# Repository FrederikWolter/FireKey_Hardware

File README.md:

# FireKey - Hardware

This student research project named *FireKey* is part of the winter semester 2022 and summer semester 2023 in the
Applied Computer Science course at DHBW Mannheim. The aim is to create a macro keyboard with individually configurable
keys that allow the input of simple key combinations up to more complex sequences.

This repository is used for developing the *hardware* of *FireKey*. The corresponding firmware is developed in
the [FireKey_Firmware](https://github.com/FrederikWolter/FireKey_Firmware) repository and the configuration software
in [FireKey_Configurator](https://github.com/FrederikWolter/FireKey_Configurator).

## Structure

### *PCB*

Work in progress TODO

### *PCB_theory*

Work in progress TODO

### *3D_printing*

Work in progress TODO

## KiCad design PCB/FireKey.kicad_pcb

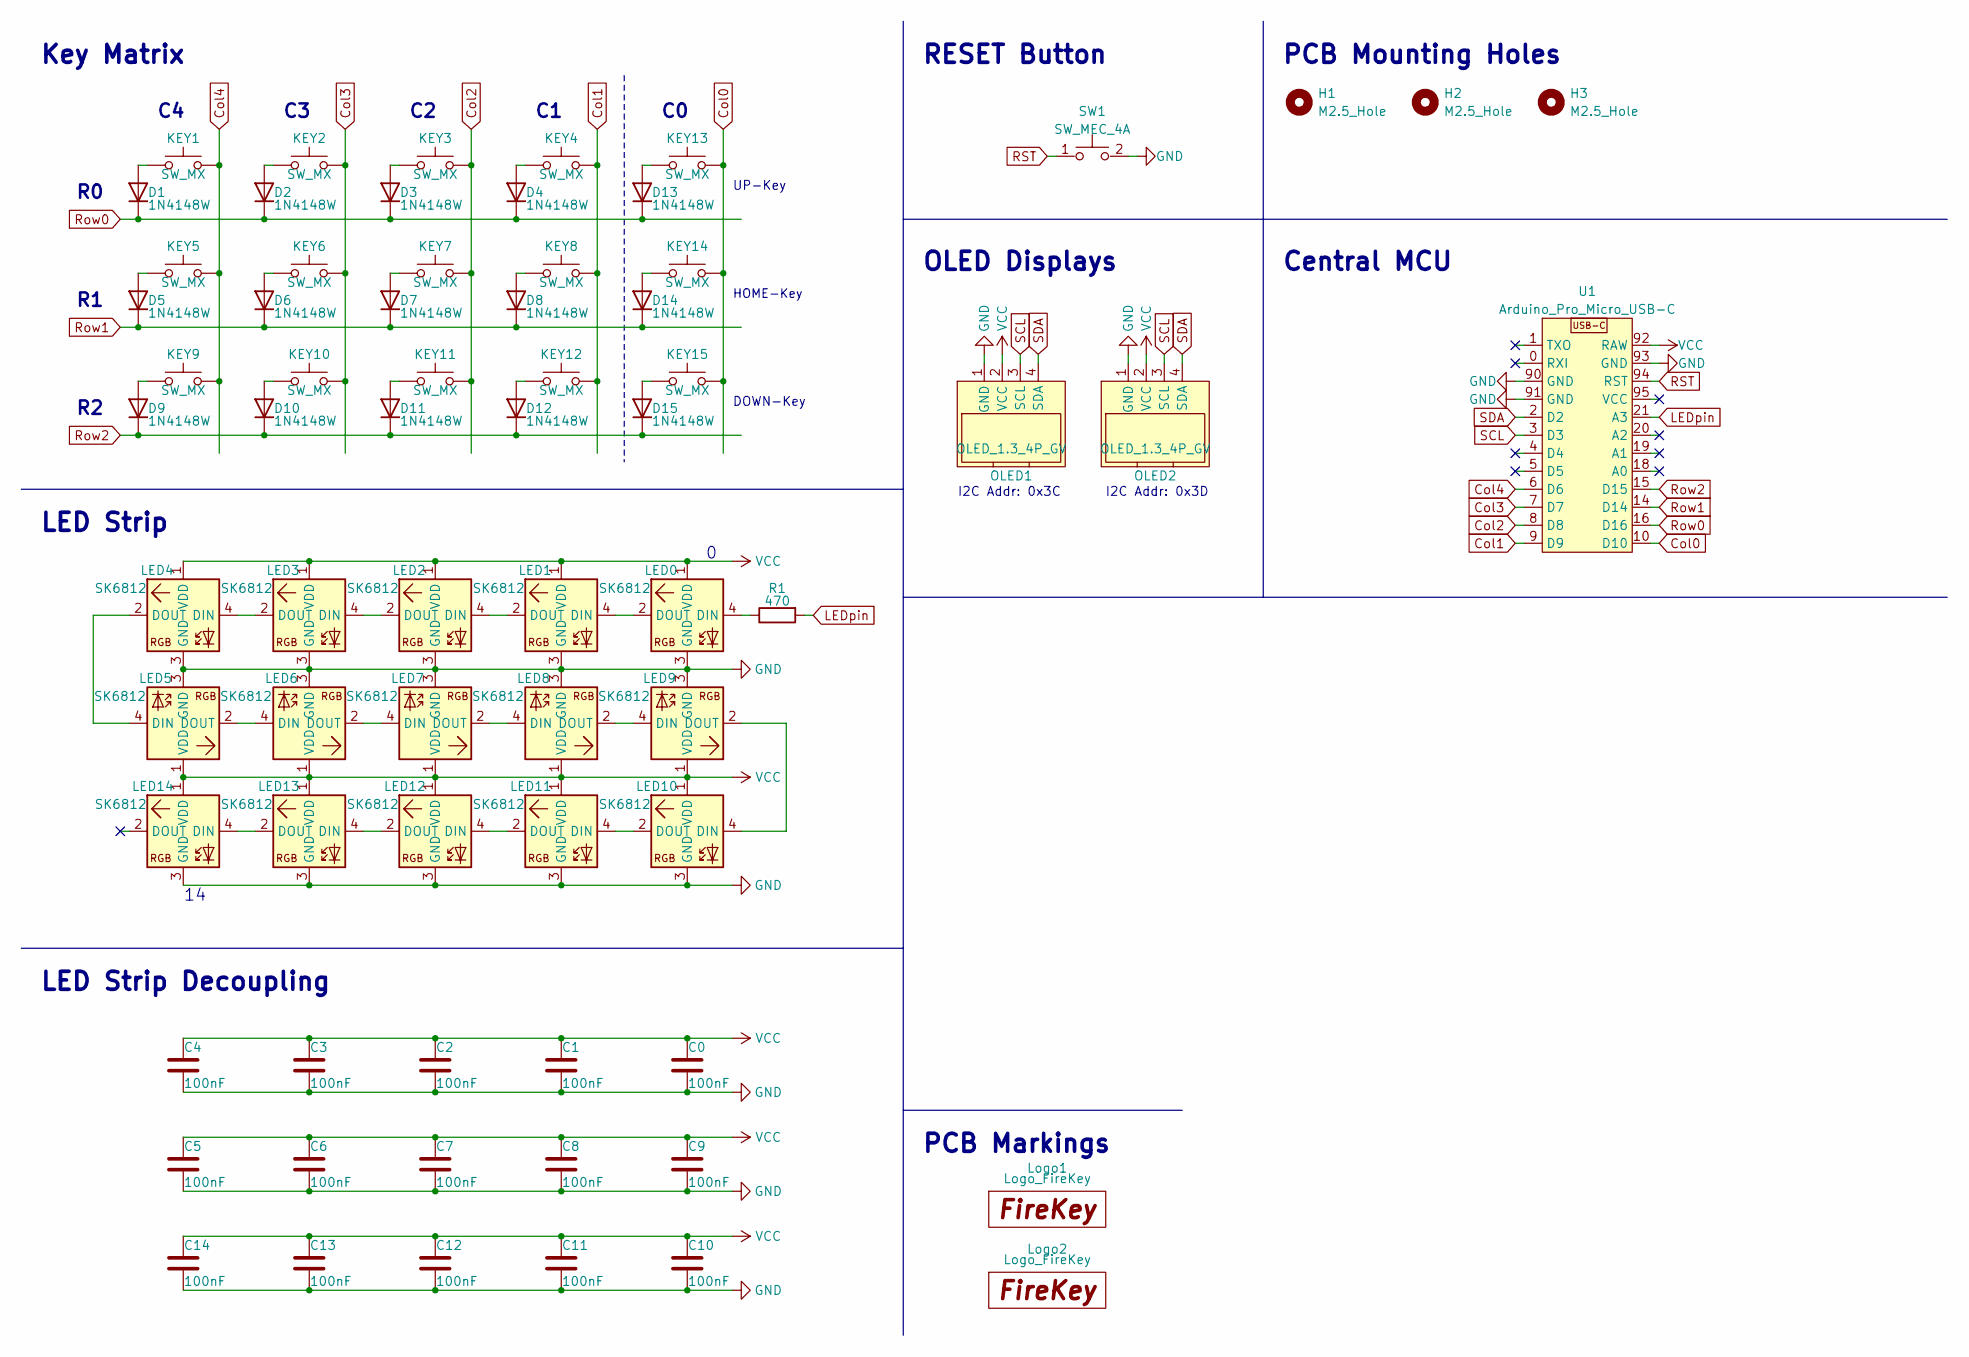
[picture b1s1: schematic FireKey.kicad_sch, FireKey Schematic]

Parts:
C0, C1, C2, C3, C4, C5, C6, C7, C8, C9, C10, C11, C12, C13, C14: 100nF; C_0603_1608Metric_Pad1.08x0.95mm_HandSolder; Part# C694249
D1, D2, D3, D4, D5, D6, D7, D8, D9, D10, D11, D12, D13, D14, D15: 1N4148W; D_SOD-123; Part# C2892570
H1, H2, H3: M2.5_Hole; MountingHole_2.7mm_M2.5
KEY1, KEY2, KEY3, KEY4, KEY5, KEY6, KEY7, KEY8, KEY9, KEY10, KEY11, KEY12, KEY13, KEY14, KEY15: SW_MX; SW_Cherry_MX_1.00u_PCB_CleanFront
LED0, LED1, LED2, LED3, LED4, LED5, LED6, LED7, LED8, LED9, LED10, LED11, LED12, LED13, LED14: SK6812; DY-S352818-6812-2T; Part# C524051
Logo1: Logo_FireKey; Logo_FireKey_22x6.4
Logo2: Logo_FireKey; Logo_FireKey_12x3.5
OLED1, OLED2: OLED_1.3_4P_GV; OLED_1.3_4P_M2.5Holes_CleanFront
R1: 470; R_0603_1608Metric_Pad0.98x0.95mm_HandSolder; Part# C23179
SW1: SW_MEC_4A; SW_SPST_TL3342; Part# C2888878
U1: Arduino_Pro_Micro_USB-C; Arduino_Pro_Micro_USB-C_CleanFront

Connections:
Col0: KEY13.2 (B), KEY14.2 (B), KEY15.2 (B), U1.10 (D10)
Col1: KEY4.2 (B), KEY8.2 (B), KEY12.2 (B), U1.9 (D9)
Col2: KEY3.2 (B), KEY7.2 (B), KEY11.2 (B), U1.8 (D8)
Col3: KEY2.2 (B), KEY6.2 (B), KEY10.2 (B), U1.7 (D7)
Col4: KEY1.2 (B), KEY5.2 (B), KEY9.2 (B), U1.6 (D6)
GND: C0.2, C1.2, C2.2, C3.2, C4.2, C5.2, C6.2, C7.2, C8.2, C9.2, C10.2, C11.2, C12.2, C13.2, C14.2, LED0.3 (GND), LED1.3 (GND), LED2.3 (GND), LED3.3 (GND), LED4.3 (GND), LED5.3 (GND), LED6.3 (GND), LED7.3 (GND), LED8.3 (GND), LED9.3 (GND), LED10.3 (GND), LED11.3 (GND), LED12.3 (GND), LED13.3 (GND), LED14.3 (GND), OLED1.1 (GND), OLED2.1 (GND), SW1.2, U1.90 (GND), U1.91 (GND), U1.93 (GND)
LEDpin: R1.2, U1.21 (A3)
unnamed: D1.2 (A), KEY1.1 (A)
unnamed: D2.2 (A), KEY2.1 (A)
unnamed: D3.2 (A), KEY3.1 (A)
unnamed: D4.2 (A), KEY4.1 (A)
unnamed: D5.2 (A), KEY5.1 (A)
unnamed: D6.2 (A), KEY6.1 (A)
unnamed: D7.2 (A), KEY7.1 (A)
unnamed: D8.2 (A), KEY8.1 (A)
unnamed: D9.2 (A), KEY9.1 (A)
unnamed: D10.2 (A), KEY10.1 (A)
unnamed: D11.2 (A), KEY11.1 (A)
unnamed: D12.2 (A), KEY12.1 (A)
unnamed: D13.2 (A), KEY13.1 (A)
unnamed: D14.2 (A), KEY14.1 (A)
unnamed: D15.2 (A), KEY15.1 (A)
unnamed: LED0.2 (DOUT), LED1.4 (DIN)
unnamed: LED0.4 (DIN), R1.1
unnamed: LED1.2 (DOUT), LED2.4 (DIN)
unnamed: LED2.2 (DOUT), LED3.4 (DIN)
unnamed: LED3.2 (DOUT), LED4.4 (DIN)
unnamed: LED4.2 (DOUT), LED5.4 (DIN)
unnamed: LED5.2 (DOUT), LED6.4 (DIN)
unnamed: LED6.2 (DOUT), LED7.4 (DIN)
unnamed: LED7.2 (DOUT), LED8.4 (DIN)
unnamed: LED8.2 (DOUT), LED9.4 (DIN)
unnamed: LED10.2 (DOUT), LED11.4 (DIN)
unnamed: LED9.2 (DOUT), LED10.4 (DIN)
unnamed: LED11.2 (DOUT), LED12.4 (DIN)
unnamed: LED12.2 (DOUT), LED13.4 (DIN)
unnamed: LED13.2 (DOUT), LED14.4 (DIN)
RST: SW1.1, U1.94 (RST)
Row0: D1.1 (K), D2.1 (K), D3.1 (K), D4.1 (K), D13.1 (K), U1.16 (D16)
Row1: D5.1 (K), D6.1 (K), D7.1 (K), D8.1 (K), D14.1 (K), U1.14 (D14)
Row2: D9.1 (K), D10.1 (K), D11.1 (K), D12.1 (K), D15.1 (K), U1.15 (D15)
SCL: OLED1.3 (SCL), OLED2.3 (SCL), U1.3 (D3)
SDA: OLED1.4 (SDA), OLED2.4 (SDA), U1.2 (D2)
VCC: C0.1, C1.1, C2.1, C3.1, C4.1, C5.1, C6.1, C7.1, C8.1, C9.1, C10.1, C11.1, C12.1, C13.1, C14.1, LED0.1 (VDD), LED1.1 (VDD), LED2.1 (VDD), LED3.1 (VDD), LED4.1 (VDD), LED5.1 (VDD), LED6.1 (VDD), LED7.1 (VDD), LED8.1 (VDD), LED9.1 (VDD), LED10.1 (VDD), LED11.1 (VDD), LED12.1 (VDD), LED13.1 (VDD), LED14.1 (VDD), OLED1.2 (VCC), OLED2.2 (VCC), U1.92 (RAW)

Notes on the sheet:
RESET Button
DOWN-Key
UP-Key
LED Strip
HOME-Key
I2C Addr: 0x3C
PCB Mounting Holes
Key Matrix
I2C Addr: 0x3D
OLED Displays
Central MCU
LED Strip Decoupling
PCB Markings

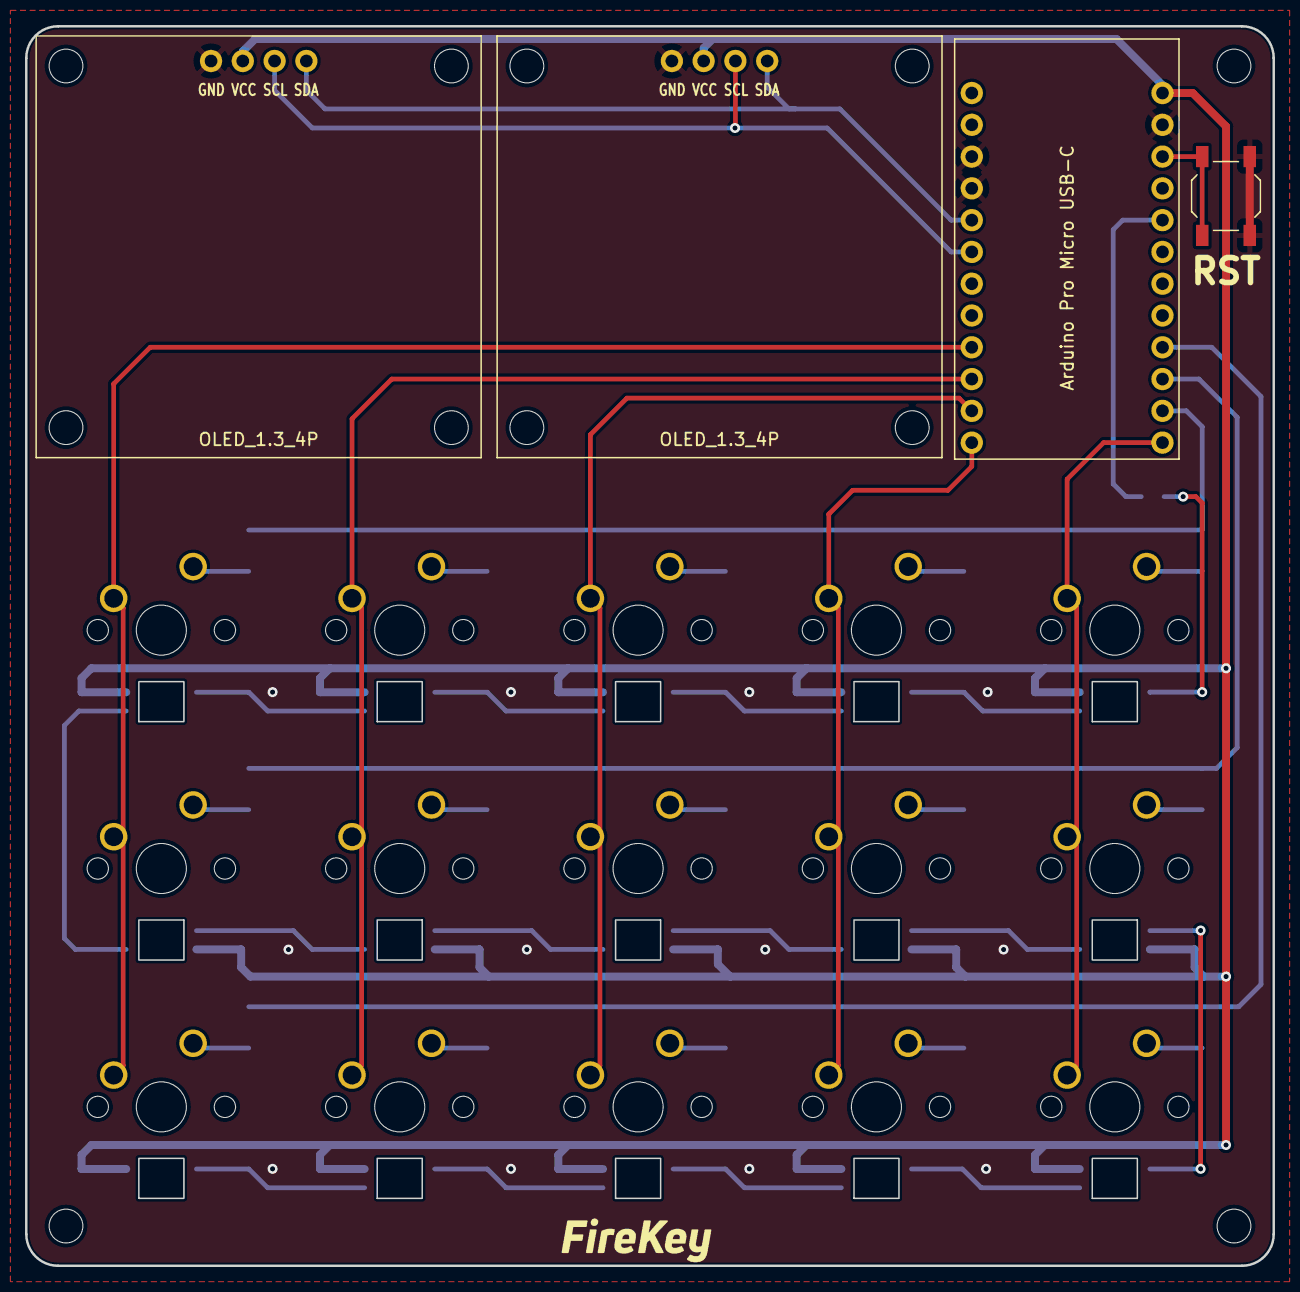
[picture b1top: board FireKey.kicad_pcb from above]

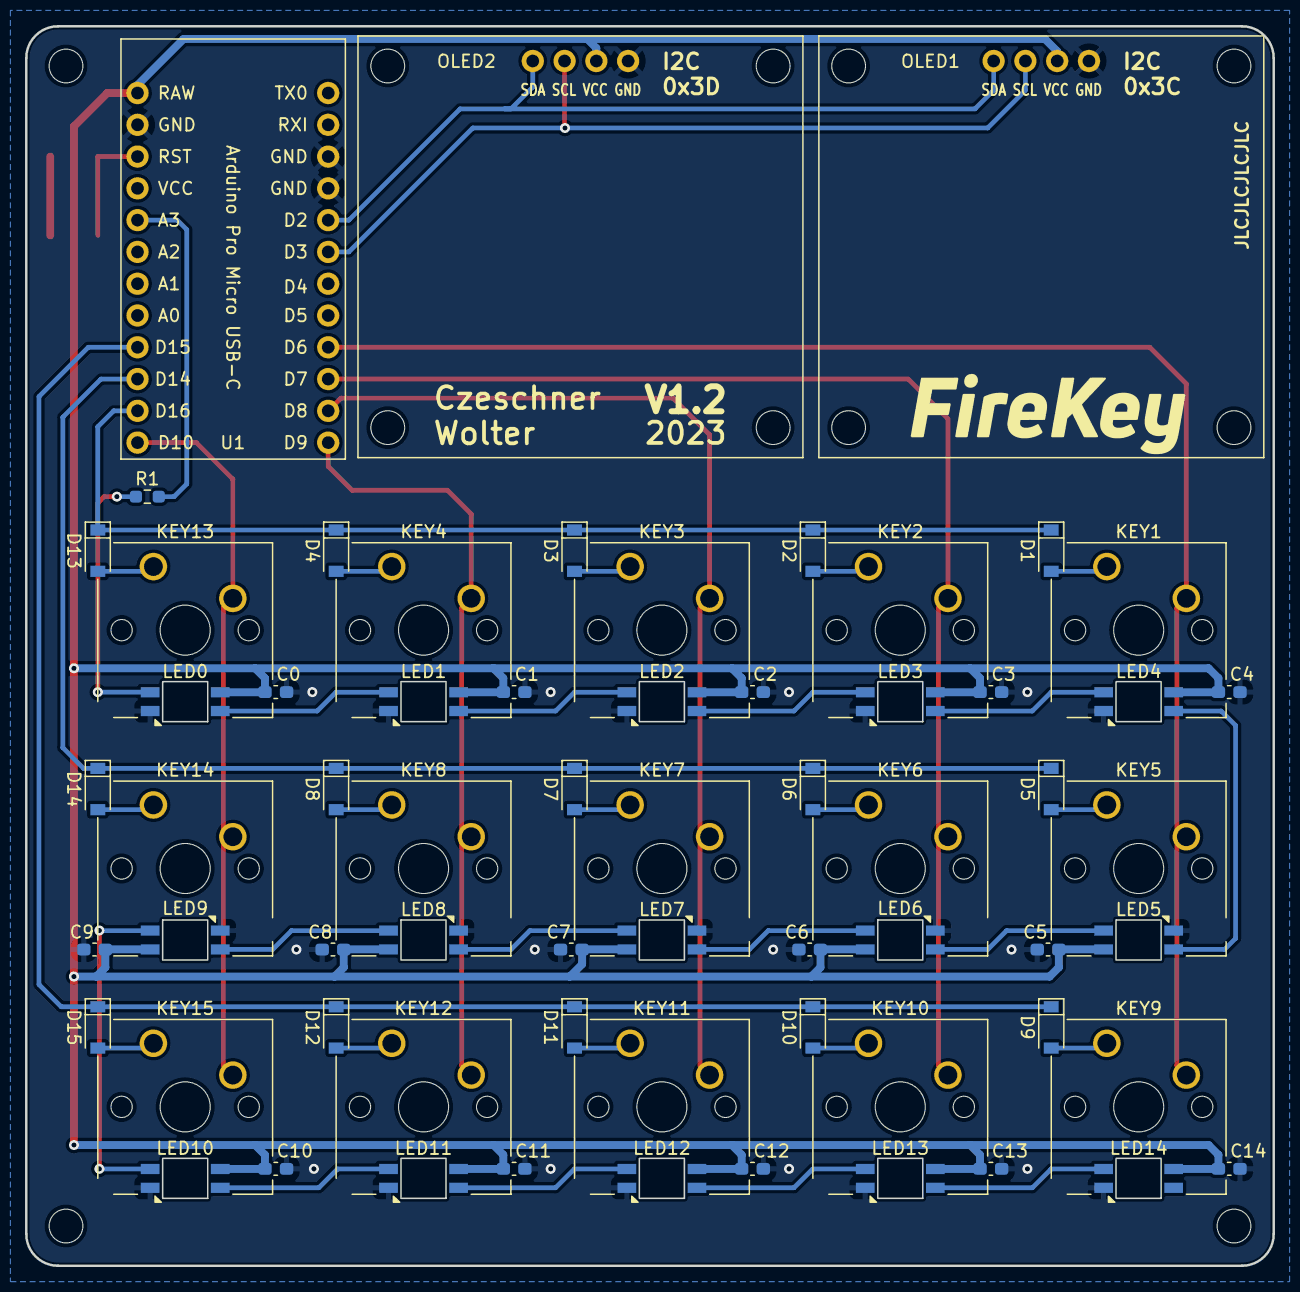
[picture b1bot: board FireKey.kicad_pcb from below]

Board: 2 copper layers, 99.7 x 99.1 mm, 70 parts (47 on the bottom side), 44 nets.

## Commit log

2022-11-13 added .gitignore for KiCad files
2022-11-13 add empty KiCad project
2022-11-13 Started recreating V0 schematic in KiCad
2022-11-14 added custom libraries
2022-11-14 worked on schematic
2022-11-14 worked on schematic; added net labels
2022-11-14 change .gitignore to not ignore BOM files
2022-11-14 finished recreating V0 schematic in KiCad
2022-11-14 generated current version of BOM
2022-11-14 updated and worked on BOM
2022-11-14 BOM management; started footprint assignment
2022-11-15 shortend link refrences to datasheets
2022-11-15 Added second theory KiCad project
2022-11-15 fixed FireKe_Theory KiCad project location
2022-11-15 Set up theory project
2022-11-15 playing around with schematic segmentation
2022-11-17 worked on schematic structure
2022-11-17 Worked on BOM
2022-11-17 start adding custom footprints
2022-11-19 added led footprint
2022-11-19 worked on oled footprint
2022-11-19 added oled footprint with mounting holes
2022-11-19 updated schematic
2022-11-19 created pcb design file
2022-11-19 worked on pcb settings and capabilities
2022-11-20 simplified led strip tracing
2022-11-20 make key matrix schematic represent actual layout
2022-11-20 mirrored leds to match pcb; changed key numbering to match led index
2022-11-20 worked on pcb design
2022-11-27 small changes to schematic
2022-11-27 moved main components on pcb
2022-11-27 fixed diode naming in schematic
2022-11-27 worked on placing parts on pcb
2022-11-27 placed all parts on pcb
2022-11-27 started routing pcb
2022-11-27 created own mx switch symbol
2022-11-27 fixed mx switches
2022-11-27 created own rst switch symbol
2022-11-27 fixed rst switch
2022-11-29 worked on tracing pcb
2022-11-29 worked on DRC errors
2022-11-29 finished V0.0
2022-11-30 fixed version number to V0.1
2022-12-04 renamed BOM folder
2022-12-04 added Logo as footprint; worked on DRC
2022-12-04 setup gerber export; updated rev
2022-12-04 added V0.1.1 gerbers
2022-12-08 updated BOM
2022-12-08 updated Footprints
2022-12-08 updated Symbol
2022-12-08 small changes to schematic; passed DRC
2022-12-08 Updated Footprint Pro Micro
2022-12-08 small changes to pcb; passed DRC
2022-12-08 generated Gerber for V0.1.2
2022-12-08 started working on V1.0.0
2022-12-10 Worked on V1.0.0 Schematic
2022-12-12 fixed RST SW footprint
2022-12-12 added standalone logo part
2022-12-12 Worked on V1.0.0 PCB
2022-12-12 deleted unused Mounting Holes in schematic
2022-12-12 group key sets on pcb
2022-12-16 updated key labels in schematic
2022-12-16 worked on key matrix routing
2022-12-18 minor change to schematic
2022-12-18 worked on pcb routing
2022-12-18 changed col order; switched to new sw footprint
2022-12-18 worked on PCB tracing and DRC errors
2022-12-23 removed unused mounting holes on schematic
2022-12-23 worked on DRC errors; routing
2022-12-23 finished rounting
2022-12-23 worked on logos in schematic
2022-12-23 added two smaller logo sizes
2022-12-23 added second logo to schematic
2022-12-23 small changes to PCB; placing logos
2022-12-23 pro micro added bottom silkscreen
2022-12-23 minor changes pcb
2022-12-25 schematic cleanup
2022-12-25 updated BOM V1.0.0
2022-12-25 Added ibom V1.0.0
2022-12-25 DRC pass PCB V1.0.0
2022-12-25 Generated Gerber V1.0.0
2022-12-30 cleaned up lib structure in KiCad
2022-12-30 started Inventor project
2022-12-30 added Cherr_Switch_Alignment_Jig
2022-12-30 tuning of Cherry_Alignment_Jig
2022-12-31 tuned clearance; added 5x3 version
2023-01-03 renamed dir to 3D_printing
2023-01-03 .gitignore comments
2023-01-04 Arduino Pro Micro added 3D Modell
2023-01-04 LED added 3D Modell
2023-01-04 OLED added 3D Modell
2023-01-04 Cherry Switch added 3D Modell
2023-01-04 updated PCB to use 3D Modells
2023-01-07 Generated BOM
2023-01-07 Changed to V1.0.1
2023-01-07 added more dimensions to pcb
2023-01-07 generated Gerbers for V1.0.1
2023-01-08 begin HV1.1.0
2023-01-08 smaller thermal spoke for gnd plane
2023-01-08 changed schematic to use two I2C buses
2023-01-08 updated symbols in schematic
2023-01-08 switched I2C_1 and I2C_2 for better routing
2023-01-08 routed new I2C bus on pcb
2023-01-08 DRC checks
2023-01-16 automatic changes to pcb
2023-01-16 generated gerbers for V1.1.0
2023-01-16 added display symbol with switched polarity
2023-01-16 minor changes to display footprint
2023-01-16 Starting HV1.2.0 by changing to new displays
2023-01-16 changing pcb to new displays
2023-01-16 generated V1.2.0 Gerber
2023-01-16 minor changes to labels
2023-02-05 3D_printing renamed stl
2023-02-05 added ClearFront variants of MCU and OLED
2023-02-05 changed to HV1.2.1; switched to cleanFront footprints
2023-02-05 created HV1.2.1 PCB; minor changes to silkscreen
2023-02-05 generated ibom for HV1.2.1
2023-02-05 updated example part suppliers
2023-02-05 generated BOM for HV1.2.1
2023-02-05 updated pcb with supplier changes
2023-02-05 generated gerber for HV1.2.1
2023-02-18 Started working on a potential display standoff
2023-02-18 added housing bottom
2023-02-18 worked on 3d print models
2023-02-25 worked on housing_bottom
2023-04-15 Added button theory
2023-04-15 Changes sub sheets orientation in theory
2023-04-15 minor changes to 1_botton_complete
2023-04-15 Added 3_LEDs Theory
2023-04-16 added 3_LEDs_complete
2023-04-21 added 2_oled
2023-04-21 fixed annotation in 2_oled
2023-04-21 added 4_mcu to theory
2023-04-22 added housing drawing
2023-04-22 added 5_bouce to theory
